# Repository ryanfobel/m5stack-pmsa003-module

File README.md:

# m5stack-pmsa003-module

Laser Scattering Particulate Matter Module [pm1.0/pm2.5/pm10] for the [m5stack].

These PMSA003 modules are commonly used for monitoring particulate matter in the air (e.g., dust, smoke, etc.). Connecting these sensors with a WiFi/bluetooth-enabled microcontroller like the [ESP32] enables wireless monitoring and/or the abiltity to setup automations (e.g., turn on an exhaust or a HEPA filter fan when the air quality crosses a certain threshold).

## Plantower PMSA003

* [datasheet](/reference/PMSA003%20series%20data%20manua_English_V2.6.pdf)

## References and Related Projects

1. https://github.com/kylemanna/sniffer
2. https://github.com/tomorrow56/M5Stack_Motor_Driver
3. https://github.com/ZIOCC/Zio-Qwiic-PM2.5-Air-Quality-Sensor-Adapter-Board
4. https://github.com/appsmonkey/air.nodemcu.full
5. https://cityos.io/air

[m5stack]: https://m5stack.com/
[ESP32]: https://en.wikipedia.org/wiki/ESP32

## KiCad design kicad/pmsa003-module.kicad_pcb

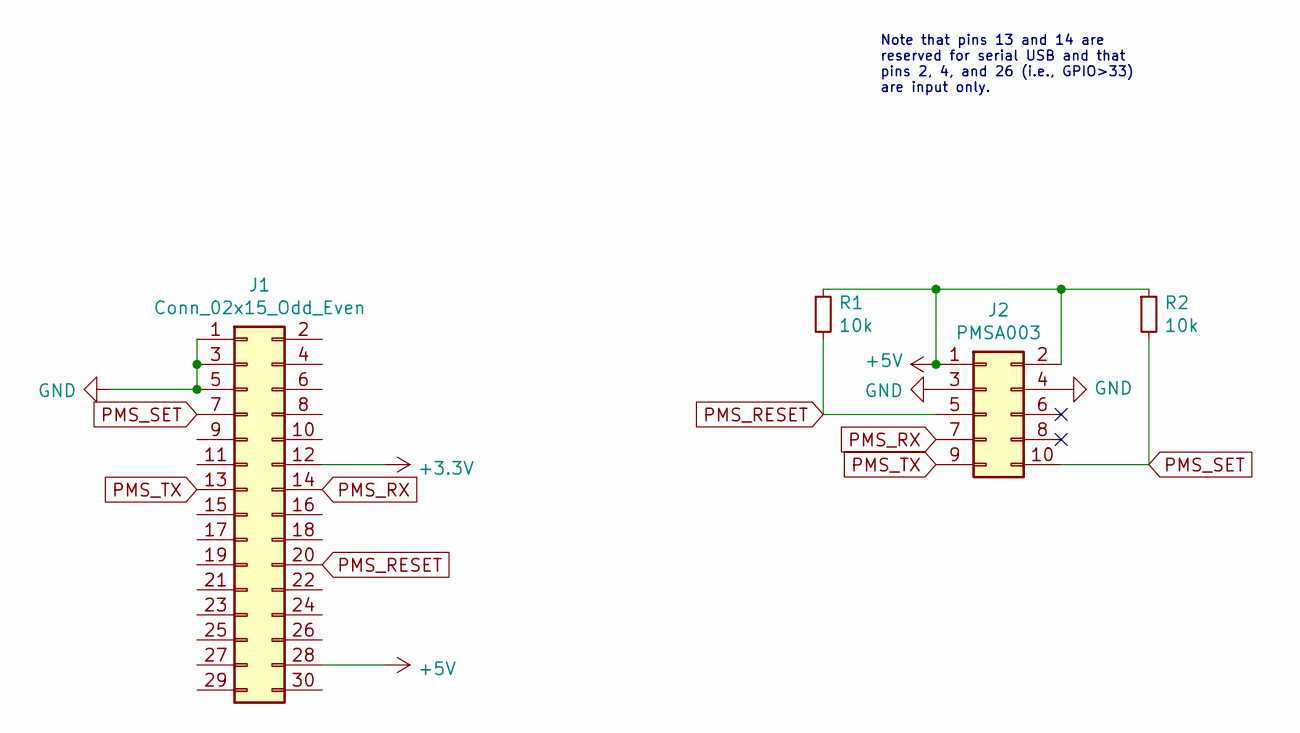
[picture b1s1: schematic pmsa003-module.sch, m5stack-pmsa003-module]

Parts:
J1: Conn_02x15_Odd_Even; M5Stack_PinHeader_2x15_P2.54mm
J2: PMSA003
R1, R2: 10k; R_0805_2012Metric

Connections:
+3V3: J1.12
+5V: J1.28, J2.1, J2.2, R1.1, R2.1
GND: J1.1, J1.3, J1.5, J2.3, J2.4
PMS_RESET: J1.20, J2.5, R1.2
PMS_RX: J1.14, J2.7
PMS_SET: J1.7, J2.10, R2.2
PMS_TX: J1.13, J2.9

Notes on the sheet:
Note that pins 13 and 14 are reserved for serial USB and that pins 2, 4, and 26 (i.e., GPIO>33) are input only.

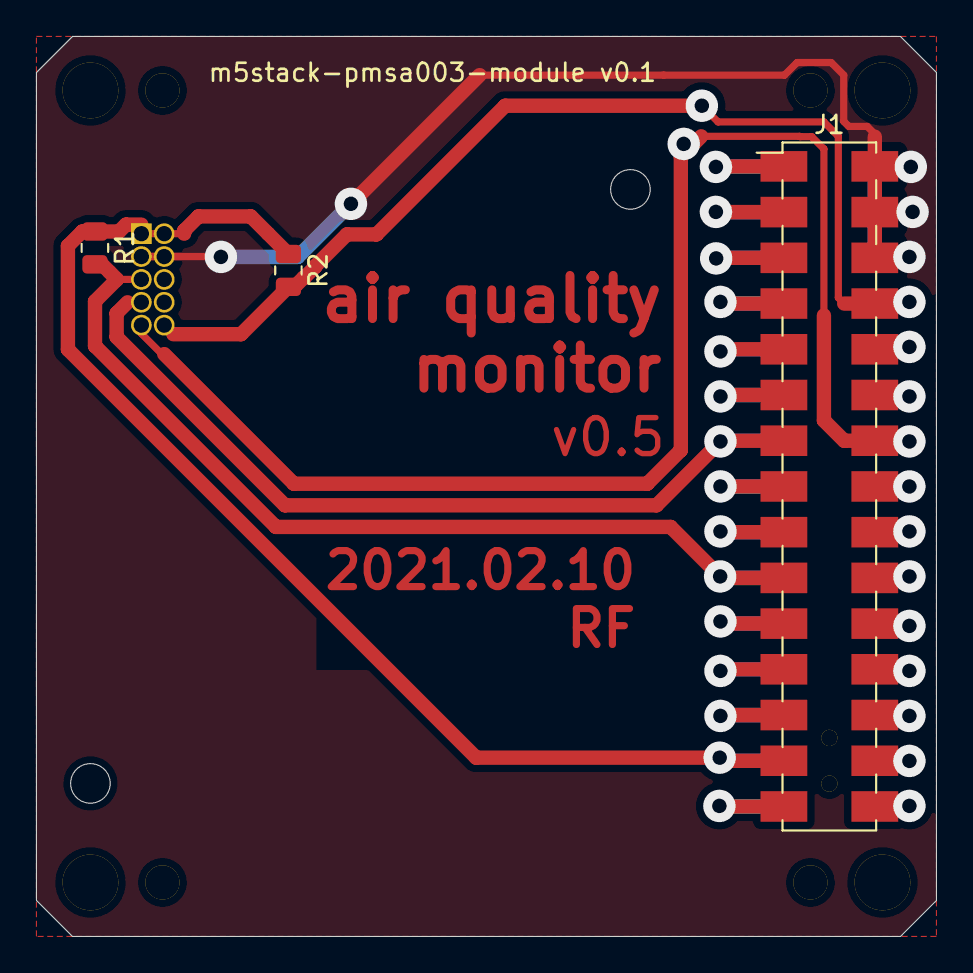
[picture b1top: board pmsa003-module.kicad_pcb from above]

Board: 2 copper layers, 50.0 x 50.0 mm, 4 parts (1 on the bottom side), 6 nets.

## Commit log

2021-02-02 Removed silkscreen and proto pads
2021-02-02 Create header footprint
2021-02-02 Reorganize footprint library
2021-04-15 Add m5stack pinheader, route, etc.
2021-04-15 Add images
